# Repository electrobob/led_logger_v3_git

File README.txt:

/*
* Led Logger v3
*
* Created: 15.03.2015
*  Author: Bogdan Raducanu
* copyright (c) Bogdan Raducanu, 2015
* www.electrobob.com
* bogdan@electrobob.com
* Released under GPLv3.
* Please refer to LICENSE file for licensing information.
*/

See full project at http://www.electrobob.com/led-logger-v3/

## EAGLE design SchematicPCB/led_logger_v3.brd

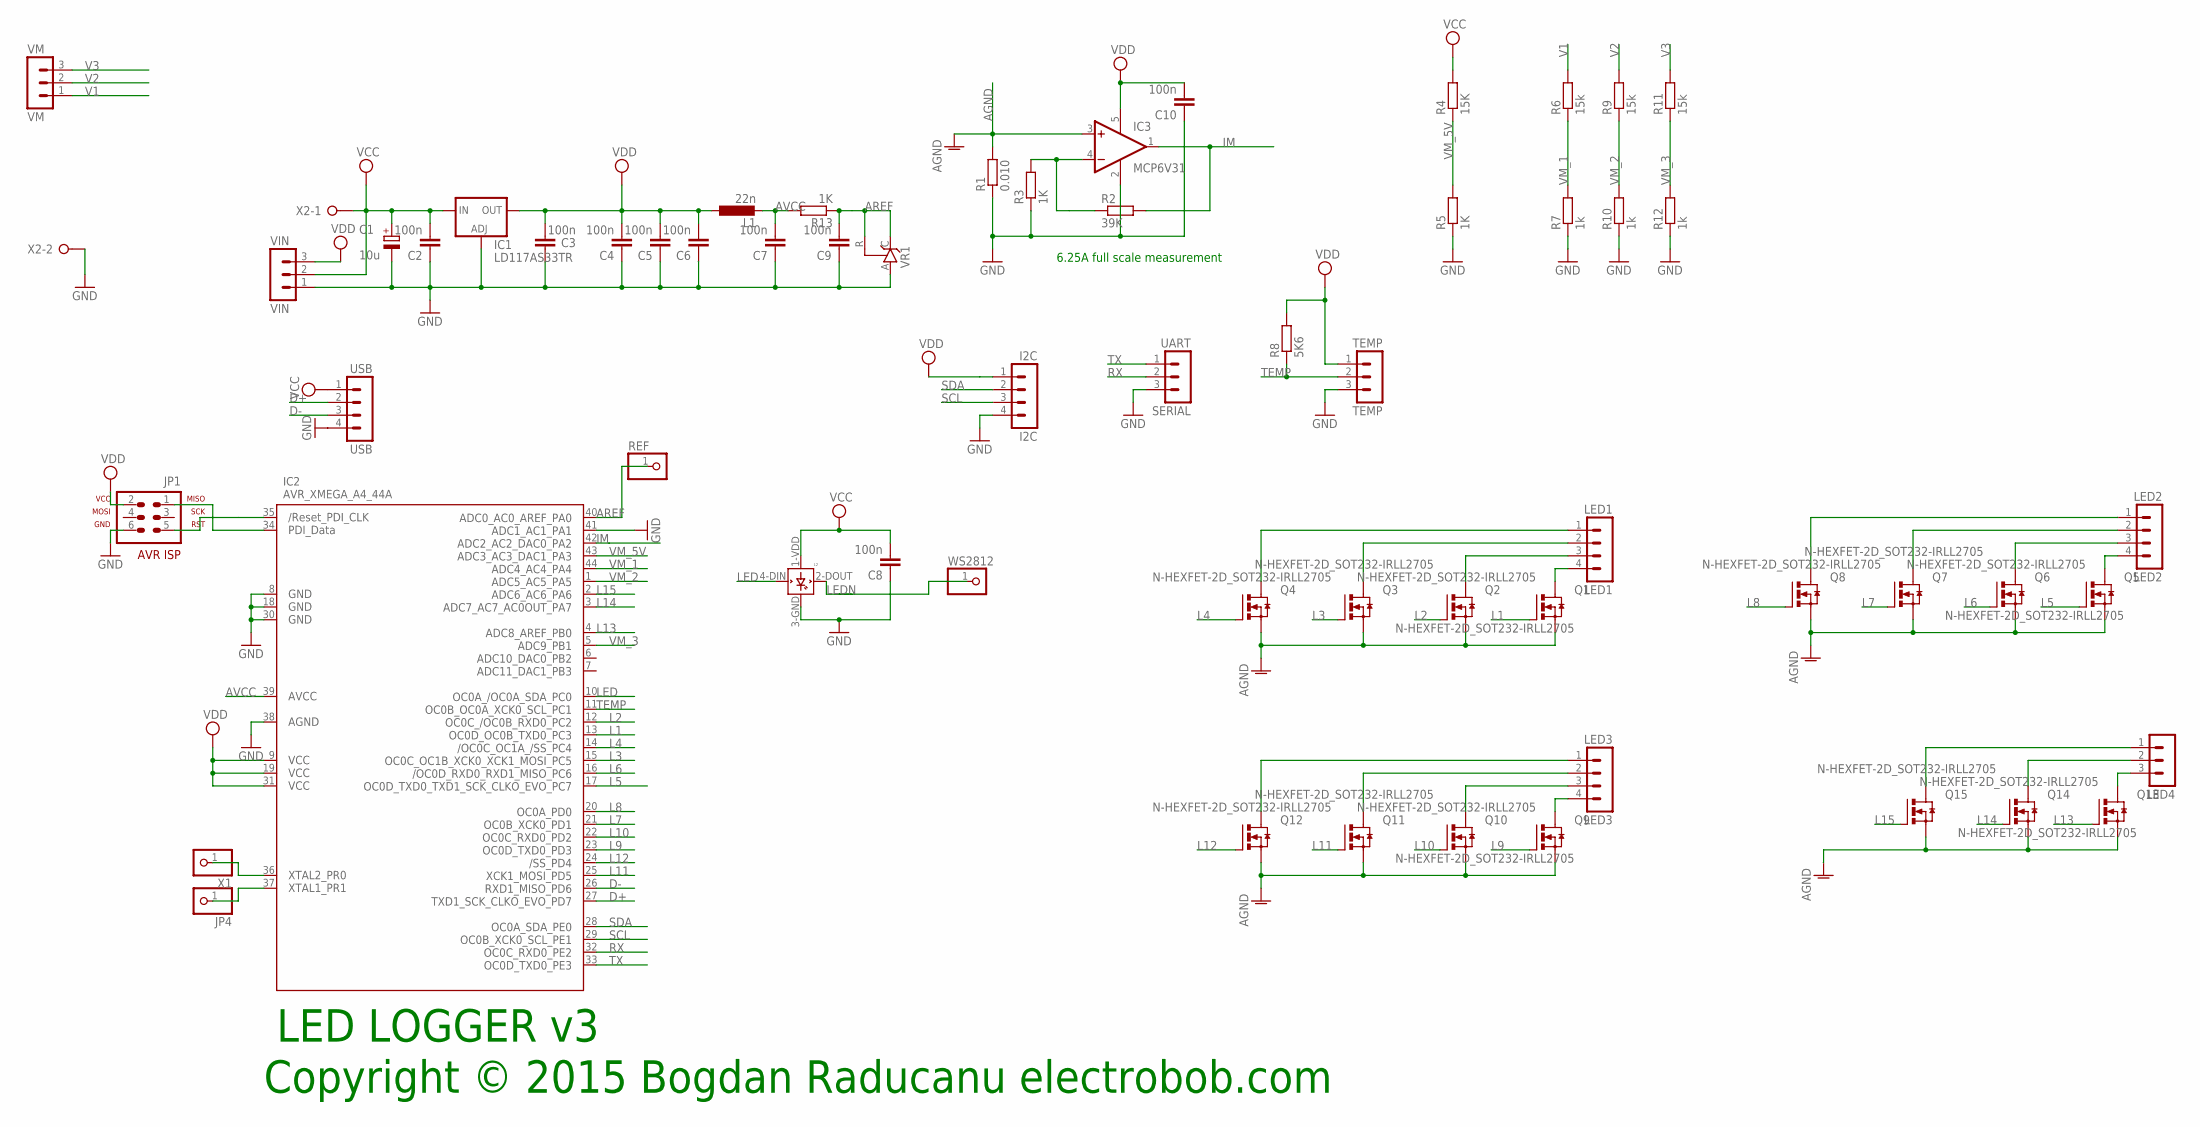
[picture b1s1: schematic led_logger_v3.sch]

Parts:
C1: 10u; SMC_A
C2, C3, C4, C5, C6, C7, C8, C10: 100n; C0805
C9: 100n; C1206
I2C: I2C; MA04-1
IC1: LD117AS33TR; SOT223
IC2: AVR_XMEGA_A4_44A; TQFP44
IC3: MCP6V31; SOT23-5
JP1: AVR-ISP-6VERT; AVR-ISP-6
JP4: PINHD-1X1; 1X01
L1: 22n; L2012C
L2: WS2812B
LED1: LED1; MA04-1
LED2: LED2; MA04-1
LED3: LED3; MA04-1
LED4: MA03-1
Q1, Q2, Q3, Q4, Q5, Q6, Q7, Q8, Q9, Q10, Q11, Q12, Q13, Q14, Q15: N-HEXFET-2D_SOT232-IRLL2705; SOT223
R1: 0.010; 0414V
R2: 39K; R0805
R3, R5, R13: 1K; R0805
R4: 15K; R0805
R6, R9, R11: 15k; R0805
R7, R10, R12: 1k; R0805
R8: 5K6; R0805
REF: PINHD-1X1; 1X01
SERIAL: UART; MA03-1
TEMP: TEMP; MA03-1
USB: USB; MA04-1
VIN: VIN; MA03-1
VM: VM; MA03-1
VR1: TL431CLP; TO92-CLP
WS2812: PINHD-1X1; 1X01
X1: PINHD-1X1; 1X01
X2: W237-02P; W237-132

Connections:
AGND: IC3.3 (+IN), Q1.3 (S), Q2.3 (S), Q3.3 (S), Q4.3 (S), Q5.3 (S), Q6.3 (S), Q7.3 (S), Q8.3 (S), Q9.3 (S), Q10.3 (S), Q11.3 (S), Q12.3 (S), Q13.3 (S), Q14.3 (S), Q15.3 (S), R1.2
AREF: C9.2, IC2.40 (PA0), R13.1, REF.1, VR1.C, VR1.R
AVCC: C7.2, IC2.39 (AVCC), L1.2, R13.2
D+: IC2.27 (PD7), USB.2
D-: IC2.26 (PD6), USB.3
GND: C1.-, C2.1, C3.1, C4.1, C5.1, C6.1, C7.1, C8.1, C9.1, C10.1, I2C.4, IC1.1 (ADJ), IC2.8 (GND1), IC2.18 (GND2), IC2.30 (GND3), IC2.38 (AGND), IC2.41 (PA1), IC3.2 (V-), JP1.6, L2.3-GND (GND), R1.1, R3.1, R5.1, R7.1, R10.1, R12.1, SERIAL.3, TEMP.3, USB.4, VIN.1, VR1.A, X2.2
IM: IC2.42 (PA2), IC3.1 (OUT), R2.2
L1: IC2.13 (PC3), Q1.1 (G)
L2: IC2.12 (PC2), Q2.1 (G)
L3: IC2.15 (PC5), Q3.1 (G)
L4: IC2.14 (PC4), Q4.1 (G)
L5: IC2.17 (PC7), Q5.1 (G)
L6: IC2.16 (PC6), Q6.1 (G)
L7: IC2.21 (PD1), Q7.1 (G)
L8: IC2.20 (PD0), Q8.1 (G)
L9: IC2.23 (PD3), Q9.1 (G)
L10: IC2.22 (PD2), Q10.1 (G)
L11: IC2.25 (PD5), Q11.1 (G)
L12: IC2.24 (PD4), Q12.1 (G)
L13: IC2.4 (PB0), Q13.1 (G)
L14: IC2.3 (PA7), Q14.1 (G)
L15: IC2.2 (PA6), Q15.1 (G)
LED: IC2.10 (PC0), L2.4-DIN (DIN)
LEDN: L2.2-DOUT (DOUT), WS2812.1
unnamed: LED2.4, Q5.2 (D), Q5.4 (D)
unnamed: LED3.3, Q10.2 (D), Q10.4 (D)
unnamed: LED2.2, Q7.2 (D), Q7.4 (D)
unnamed: LED2.1, Q8.2 (D), Q8.4 (D)
unnamed: LED3.4, Q9.2 (D), Q9.4 (D)
unnamed: LED1.4, Q1.2 (D), Q1.4 (D)
unnamed: LED1.3, Q2.2 (D), Q2.4 (D)
unnamed: LED1.2, Q3.2 (D), Q3.4 (D)
unnamed: LED1.1, Q4.2 (D), Q4.4 (D)
unnamed: LED2.3, Q6.2 (D), Q6.4 (D)
unnamed: IC2.35 (RESET), JP1.5
unnamed: LED3.2, Q11.2 (D), Q11.4 (D)
unnamed: LED3.1, Q12.2 (D), Q12.4 (D)
unnamed: IC3.4 (-IN), R2.1, R3.2
unnamed: IC2.36 (PR0), X1.1
unnamed: IC2.37 (PR1), JP4.1
unnamed: LED4.3, Q13.2 (D), Q13.4 (D)
unnamed: IC2.34 (PDI_DATA), JP1.1
unnamed: LED4.1, Q15.2 (D), Q15.4 (D)
unnamed: LED4.2, Q14.2 (D), Q14.4 (D)
RX: IC2.32 (PE2), SERIAL.2
SCL: I2C.3, IC2.29 (PE1)
SDA: I2C.2, IC2.28 (PE0)
TEMP: IC2.11 (PC1), R8.1, TEMP.2
TX: IC2.33 (PE3), SERIAL.1
V1: R6.2, VM.1
V2: R9.2, VM.2
V3: R11.2, VM.3
VCC: C1.+, C2.2, C8.2, IC1.3 (IN), L2.1-VDD (VDD), R4.2, USB.1, VIN.2, X2.1
VDD: C3.2, C4.2, C5.2, C6.2, C10.2, I2C.1, IC1.4 (OUT), IC2.9 (VCC1), IC2.19 (VCC2), IC2.31 (VCC3), IC3.5 (V+), JP1.2, L1.1, R8.2, TEMP.1, VIN.3
VM_1: IC2.44 (PA4), R6.1, R7.2
VM_2: IC2.1 (PA5), R9.1, R10.2
VM_3: IC2.5 (PB1), R11.1, R12.2
VM_5V: IC2.43 (PA3), R4.1, R5.2

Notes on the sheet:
Copyright © 2015 Bogdan Raducanu electrobob.com
LED LOGGER v3
6.25A full scale measurement

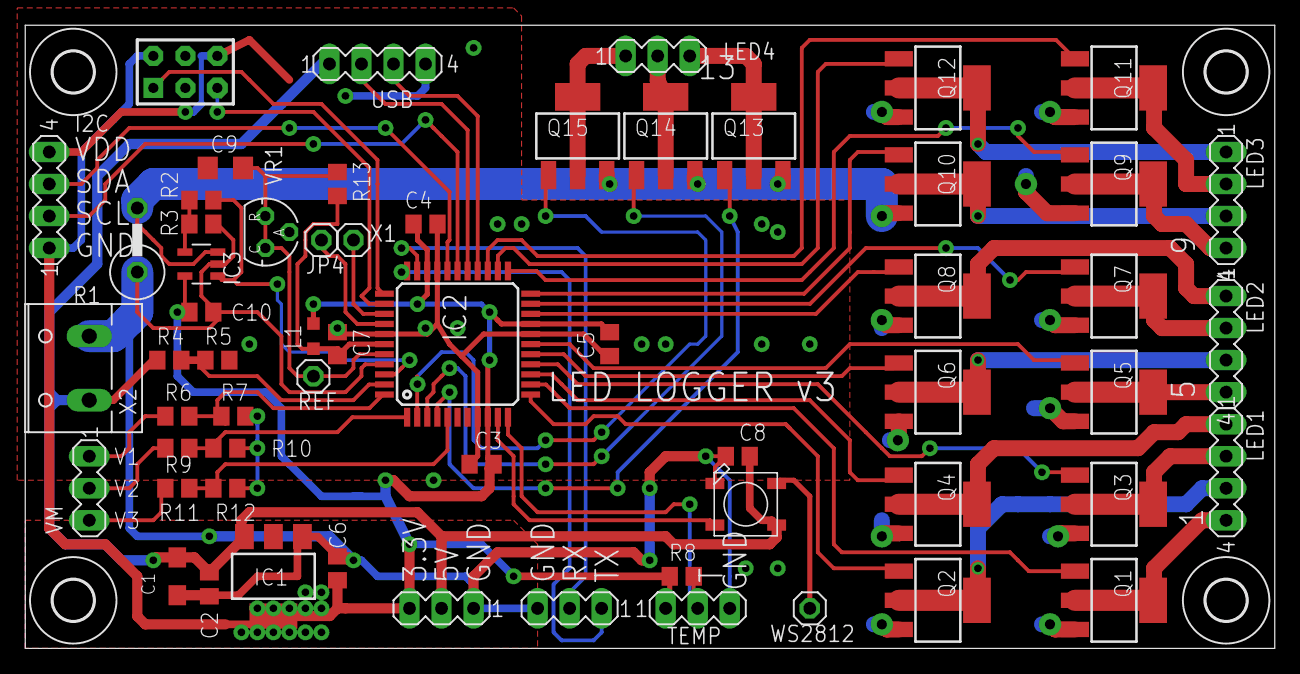
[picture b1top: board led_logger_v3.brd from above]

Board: 2 copper layers, 99.1 x 49.4 mm, 64 parts (0 on the bottom side), 58 nets.

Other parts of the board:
U$1, U$2, U$3, U$4: 3,2

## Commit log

2015-03-15 Init
